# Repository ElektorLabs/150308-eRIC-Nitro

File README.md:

150308 eRIC Nitro
=================

Arduino Micro compatible module with on-board LPRS eRIC low-power smart radio module. 
Supports eRIC4 (433 MHz) and eRIC9 (865/915 MHz) modules.

The board offers several operating modes:

- MCU controls eRIC through hardware UART

- MCU controls eRIC through software UART

- MCU cooperates with eRIC, eRIC controlled by PC 

Note that eRIC modules can function fully stand-alone, without any help from a
microcontroller. This board can handle that too.

The board is included in the Elektor Arduino Boards Package available at https://github.com/ElektorLabs/Arduino/

www.elektor-labs.com/eric-nitro

www.elektor.com

www.elektor-magazine.com

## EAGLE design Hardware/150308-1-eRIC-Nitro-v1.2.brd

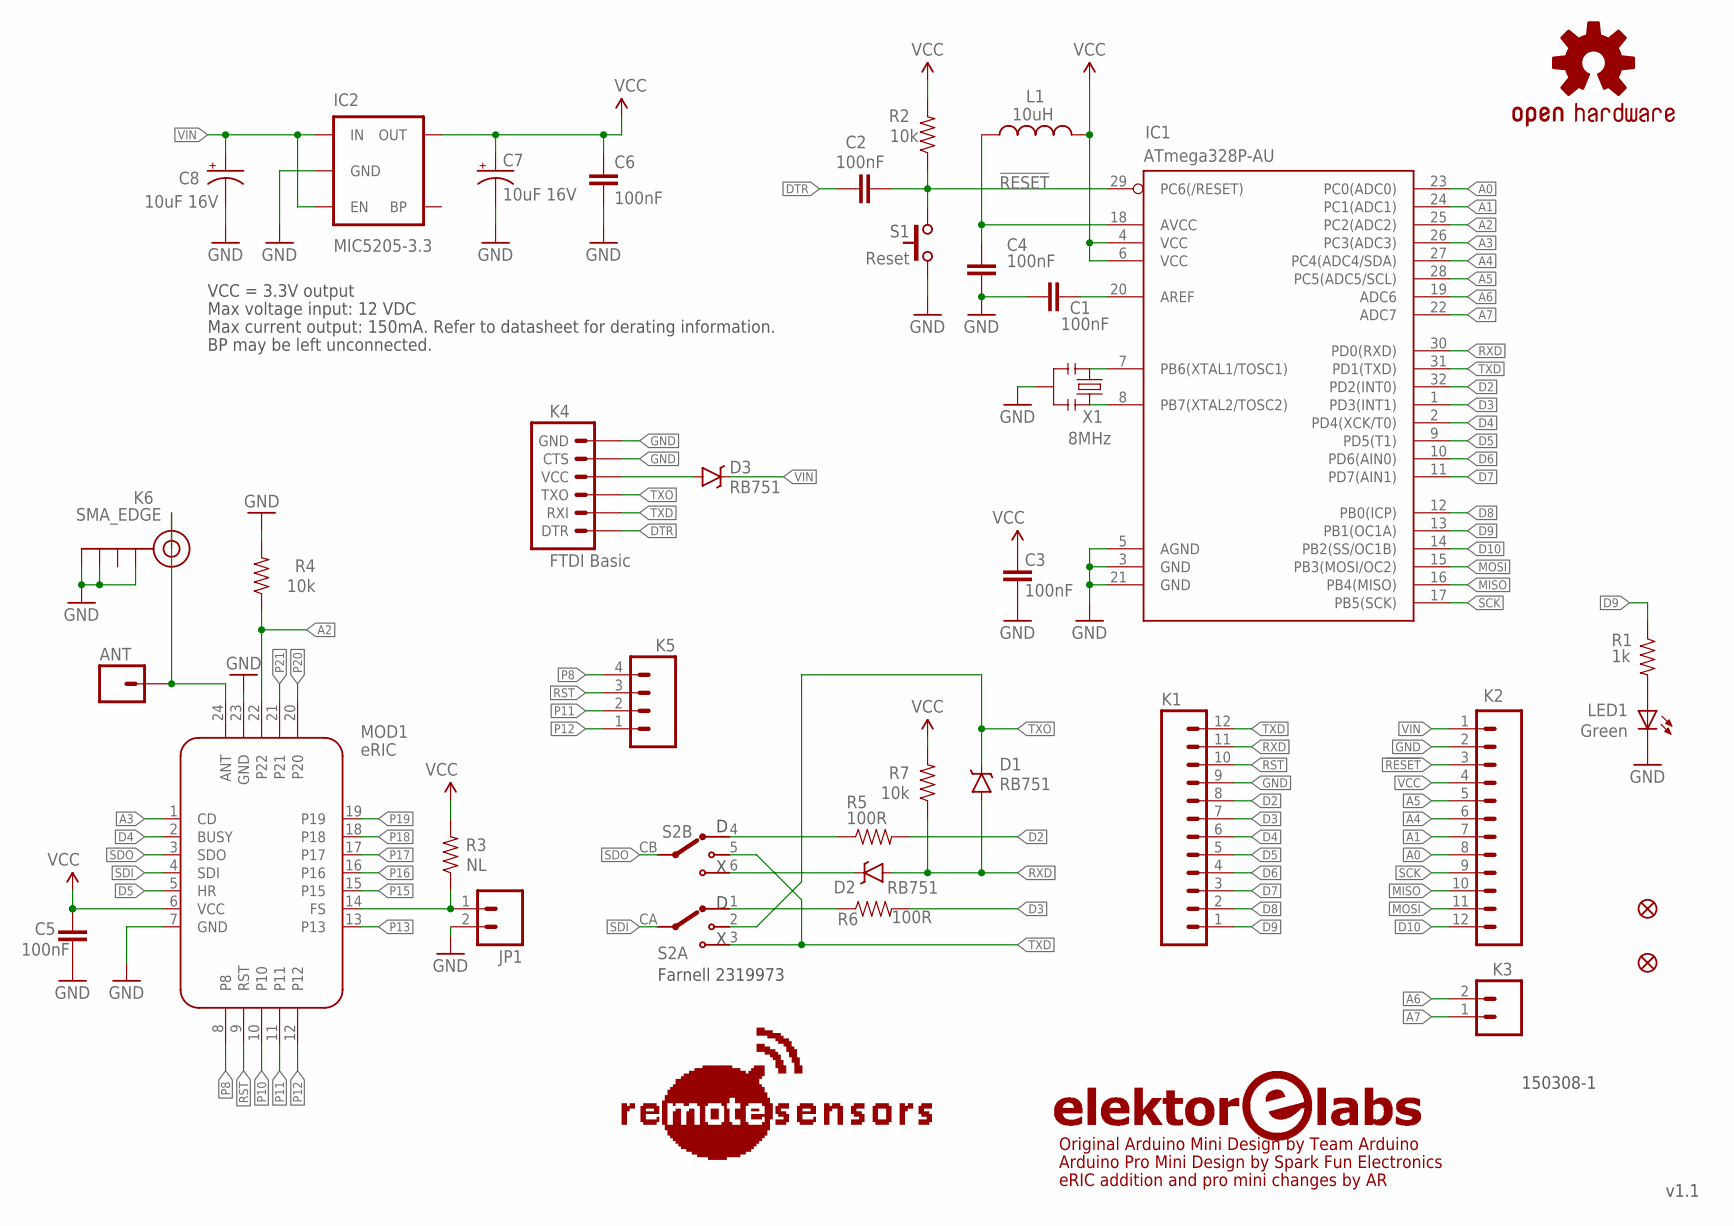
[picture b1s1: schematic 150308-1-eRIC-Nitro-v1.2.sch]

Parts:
ANT: M01PTH; 1X01-080
C1, C2, C3, C4, C5, C6: 100nF; 0603-CAP
C7, C8: 10uF 16V; EIA3216
D1, D2, D3: RB751; SOD-523
FID1, FID2: FIDUCIALUFIDUCIAL; MICRO-FIDUCIAL
IC1: ATmega328P-AU; TQFP32-08
IC2: MIC5205-3.3; SOT23-5
JP1: M02PTH; 1X02
K1, K2: M12PTH; 1X12
K3: M02PTH; 1X02
K4: FTDI Basic; 1X06
K5: M04PTH; 1X04
K6: SMA_EDGE; SMA-EDGE
L1: 10uH; 0603
LED1: Green; 0603-LED-ALT1
LOGO1: OSHW-LOGOS; OSHW-LOGO-S
LOGO2: LOGO-ELEKTOR-LABS-25MM; ELPP-LOGO-ELEKTOR-LABS-25MM
LOGO3: LOGO-REMOTE-SENSORS-17MM; LOGO-REMOTE-SENSORS2
MOD1: eRIC; ERIC
R1: 1k; 0603-RES
R2, R4, R7: 10k; 0603-RES
R3: NL; 0603-RES
R5, R6: 100R; 0603-RES
S1: Reset; TACTILE-SWITCH-SMD-ALT04
S2: AYZ0203AGRLC; AYZ0203
X1: 8MHz; RESONATOR-SMD

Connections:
!RESET!: C2.1, IC1.29 (PC6(/RESET)), K2.3, R2.1, S1.3 (2), S1.4 (2)
A0: IC1.23 (PC0(ADC0)), K2.8
A1: IC1.24 (PC1(ADC1)), K2.7
A2: IC1.25 (PC2(ADC2)), MOD1.22, R4.1
A3: IC1.26 (PC3(ADC3)), MOD1.1 (CD)
A4: IC1.27 (PC4(ADC4/SDA)), K2.6
A5: IC1.28 (PC5(ADC5/SCL)), K2.5
A6: IC1.19 (ADC6), K3.2
A7: IC1.22 (ADC7), K3.1
ANTENNE: ANT.1, K6.SIG (SIGNAL), MOD1.24 (ANT)
D2: IC1.32 (PD2(INT0)), K1.8, R5.2
D3: IC1.1 (PD3(INT1)), K1.7, R6.2
D4: IC1.2 (PD4(XCK/T0)), K1.6, MOD1.2 (BUSY)
D5: IC1.9 (PD5(T1)), K1.5, MOD1.5 (HR)
D6: IC1.10 (PD6(AIN0)), K1.4
D7: IC1.11 (PD7(AIN1)), K1.3
D8: IC1.12 (PB0(ICP)), K1.2
D9: IC1.13 (PB1(OC1A)), K1.1, R1.1
D10: IC1.14 (PB2(SS/OC1B)), K2.12
DTR: C2.2, K4.1 (DTR)
FS: JP1.1, MOD1.14 (FS), R3.1
GND: C1.1, C3.1, C4.1, C5.1, C6.2, C7.C (-), C8.C (-), IC1.3 (GND), IC1.5 (AGND), IC1.21 (GND), IC2.2 (GND), JP1.2, K1.9, K2.2, K4.5 (CTS), K4.6 (GND), K6.GND@0 (GND), K6.GND@2 (GND), K6.GND@3 (GND), LED1.C, MOD1.7 (GND), MOD1.23 (GND), R4.2, S1.1, S1.2 (1), X1.2
MISO: IC1.16 (PB4(MISO)), K2.10
MOSI: IC1.15 (PB3(MOSI/OC2)), K2.11
unnamed: IC1.8 (PB7(XTAL2/TOSC2)), X1.3
unnamed: IC1.7 (PB6(XTAL1/TOSC1)), X1.1
unnamed: C1.2, IC1.20 (AREF)
unnamed: C4.2, IC1.18 (AVCC), L1.1
unnamed: LED1.A, R1.2
unnamed: D3.A, K4.4 (VCC)
unnamed: R5.1, S2.4 (1)
unnamed: D2.C, S2.6 (3)
unnamed: R6.1, S2.1
P8: K5.4, MOD1.8
P10: MOD1.10
P11: K5.2, MOD1.11
P12: K5.1, MOD1.12
P13: MOD1.13
P15: MOD1.15
P16: MOD1.16
P17: MOD1.17
P18: MOD1.18
P19: MOD1.19
P20: MOD1.20
P21: MOD1.21
RST: K1.10, K5.3, MOD1.9 (RST)
RXD: D1.A, D2.A, IC1.30 (PD0(RXD)), K1.11, R7.1
SCK: IC1.17 (PB5(SCK)), K2.9
SDI: MOD1.4 (SDI), S2.CA (2)
SDO: MOD1.3 (SDO), S2.CB (2)
TXD: IC1.31 (PD1(TXD)), K1.12, K4.2 (RXI), S2.3, S2.5 (7)
TXO: D1.C, K4.3 (TXO), S2.2 (7)
VCC: C3.2, C5.2, C6.1, C7.A (+), IC1.4 (VCC), IC1.6 (VCC), IC2.5 (OUT), K2.4, L1.2, MOD1.6 (VCC), R2.2, R3.2, R7.2
VIN: C8.A (+), D3.C, IC2.1 (IN), IC2.3 (EN), K2.1

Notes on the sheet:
Original Arduino Mini Design by Team Arduino
Arduino Pro Mini Design by Spark Fun Electronics
Max voltage input: 12 VDC
Max current output: 150mA. Refer to datasheet for derating information.
VCC = 3.3V output
eRIC addition and pro mini changes by AR
Farnell 2319973
BP may be left unconnected.

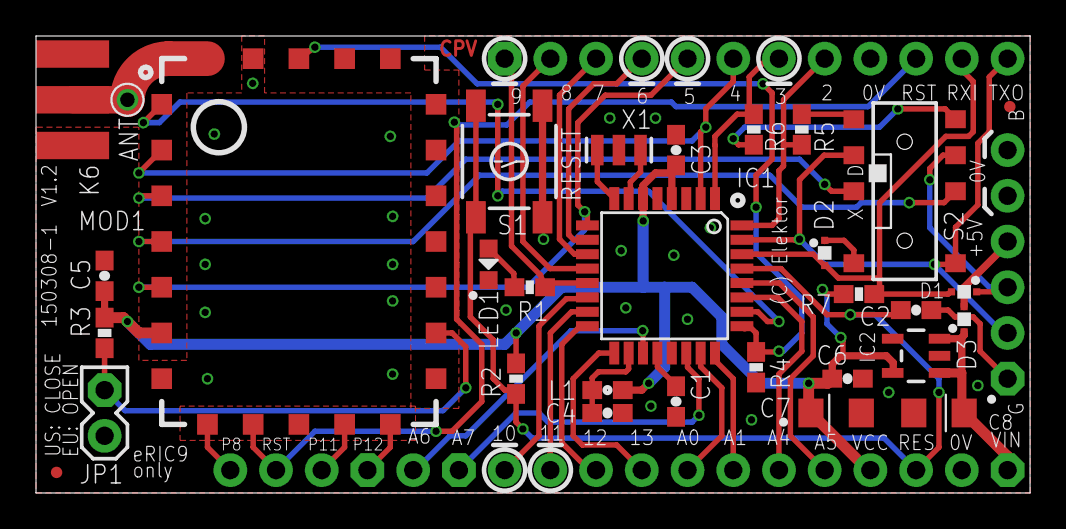
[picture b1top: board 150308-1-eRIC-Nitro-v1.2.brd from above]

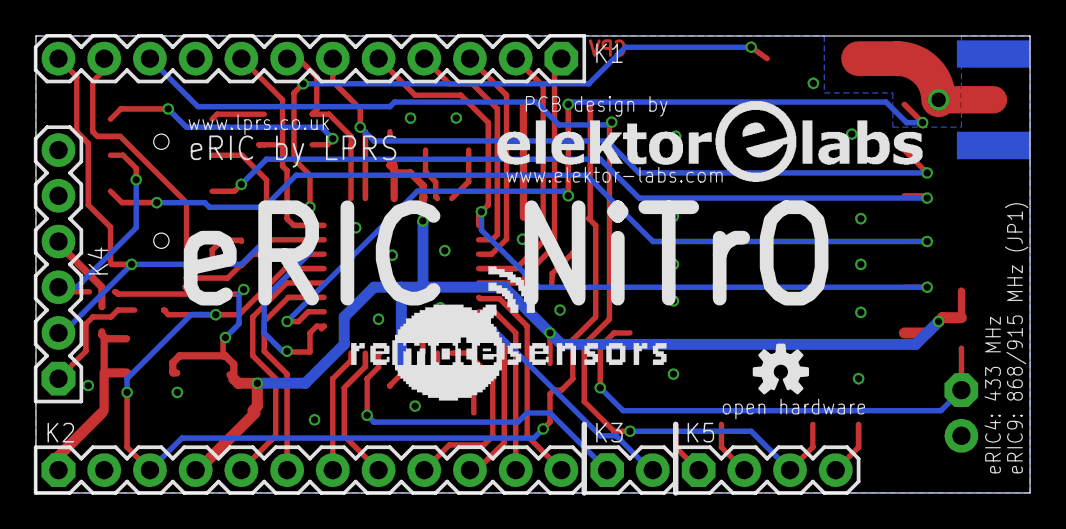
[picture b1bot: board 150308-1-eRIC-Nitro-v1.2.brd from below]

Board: 2 copper layers, 55.2 x 25.4 mm, 39 parts (8 on the bottom side), 45 nets.

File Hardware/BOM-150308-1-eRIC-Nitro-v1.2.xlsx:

BOM::150308-1::eRIC Nitro::v1.2
Description | Manufacturer | Reference | Footprint | Designation | Qnt | Farnell | Digikey | RS | BOMformul | Comments | BOM for editors
Resistor (5%, 50 V, 0.1 W, 0603) |  |  |  |  | 72 |  |  |  | Resistor (5%, 50 V, 0.1 W, 0603)
100 Ω | Bourns | CR0603-JW-102GLF | 0603-RES | R5, R6 | 2 | 2008355 |  |  | R5, R6 = 100 Ω
1 kΩ | Bourns | CR0603-JW-101GLF | 0603-RES | R1 | 1 | 2008349 |  |  | R1 = 1 kΩ
10 kΩ | Bourns | CR0603-JW-103ELF | 0603-RES | R2, R4, R7 | 3 | 2008360 |  |  | R2, R4, R7 = 10 kΩ
10 kΩ | Bourns | CR0603-JW-103ELF | 0603-RES | R3 | Not loaded | 2008360 |  |  | R3 = 10 kΩ
Capacitor |  |  |  |  | 34 |  |  |  | Capacitor
100 nF, 0603 | Multicomp | MC0603B104K500CT | 0603-CAP | C1, C2, C3, C4, C5, C6 | 6 | 1759122 |  |  | C1, C2, C3, C4, C5, C6 = 100 nF, 0603
10 µF, 16 V, tantalum | Kemet | T491A106K016AT | EIA3216 | C7, C8 | 2 | 1457414 |  |  | C7, C8 = 10 µF, 16 V, tantalum
Inductor |  |  |  |  | 23 |  |  |  | Inductor
10 µH, 0603 | TDK | MLZ1608M100WT | 0603-CAP | L1 | 1 | 2215635 |  |  | L1 = 10 µH, 0603
Semiconductor |  |  |  |  | 1 |  |  |  | Semiconductor
ATmega328P-AU | Atmel | ATMEGA328P-AU | TQFP32-08 | IC1 | 1 | 1715486 |  |  | IC1 = ATmega328P-AU
MIC5205-3.3 | Micrel | MIC5205-3.3YM5 TR | SOT23-5 | IC2 | 1 | 1663083 |  |  | IC2 = MIC5205-3.3
RB751 | ON Semiconductor | RB751S40T1G | SOD-523 | D1, D2, D3 | 3 | 2317437 |  |  | D1, D2, D3 = RB751
LED, green, 0603 | Kingbright | KPT-1608SGC | 0603-LED-ALT1 | LED1 | 1 | 2099223 |  |  | LED1 = LED, green, 0603
Misc. |  |  |  |  | 14 |  |  |  | Misc.
Resonator 8 MHz, SMT | Murata | CSTCE8M00G52-R0 | RESONATOR-SMD-1:1 | X1 | 1 | 2443268 |  |  | X1 = Resonator 8 MHz, SMT
Pin header, 1x12, 0.1" pitch | Wurth | 61301211121 | 1X12 | K1, K2 | 2 | 2356162 |  |  | K1, K2 = Pin header, 1x12, 0.1" pitch
Pin header, 1x2, 0.1" pitch | Wurth | 61300211121 | 1X02 | K3 | 1 | 2356153 |  |  | K3 = Pin header, 1x2, 0.1" pitch
Pin header, 1x2, 0.1" pitch | Wurth | 61300211121 | 1X02 | JP1 | 1 | 2356153 |  |  | JP1 = Pin header, 1x2, 0.1" pitch
Jumper, 2 way, 0.1", for JP6 | FCI | 68786-302LF | n/a |  | 1 | 1740371 |  |  | Jumper, 2 way, 0.1", for JP6
Pin header, 1x4, 0.1" pitch | Wurth | 61300411121 | 1X04 | K5 | 1 | 2356155 |  |  | K5 = Pin header, 1x4, 0.1" pitch
Pin header, 1x6, 0.1" pitch | Wurth | 61300611121 | 1X06 | K4 | 1 | 2356158 |  |  | K4 = Pin header, 1x6, 0.1" pitch
SMA edge connector | Molex | 73251-2120 | SMA-EDGE | K6 | 1 | 1909303 |  |  | K6 = SMA edge connector
Tactile switch | Multicomp | TM-533I-Q-T/R | TACTILE-SWITCH-SMD-ALT01 | S1 | 1 | 9471880 |  |  | S1 = Tactile switch
SP3T Slide Switch | C&K Components | AYZ0203AGRLC | AYZ0203 | S2 | 1 | 2319975 |  |  | S2 = SP3T Slide Switch
eRIC4 SoC Radio Transceiver | LPRS | ERIC4 | ERIC | MOD1 | 1 | 2362439 |  |  | MOD1 = eRIC4 SoC Radio Transceiver
eRIC9 SoC Radio Transceiver | LPRS | ERIC9 | ERIC | MOD1 | 1 | 2362440 |  |  | MOD1 = eRIC9 SoC Radio Transceiver
PCB 150308-1 v1.2 | Elektor | 150308-1 | n/a |  | 1 | n/a |  |  | PCB 150308-1 v1.2
Firmware 150308-11 | Elektor | 150308-11 |  |  | 1 |  |  |  | Firmware 150308-11
GREEN lines for board loaded with eRIC4 module.
BLUE lines for board loaded with eRIC9 module.

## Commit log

2015-10-08 :neckbeard: Added .gitattributes & .gitignore files
2015-10-08 Initial commit
    This is pretty much release ready.
2015-10-08 Added readme
2015-10-27 Small cosmetic changes, new bootloader
2015-11-03 Added DesignSpark PCB7 project
2016-01-04 Ping examples from Alex added
2016-11-28 Deconfuse documentation

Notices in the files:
Hardware/150308-1-eRIC-Nitro-v1.2.brd:
COPYRIGHT: (C) Elektor
parts and their libraries:
SparkFun-Passives: Licensing: Creative Commons ShareAlike 4.0 International - https://creativecommons.org/licenses/by-sa/4.0
